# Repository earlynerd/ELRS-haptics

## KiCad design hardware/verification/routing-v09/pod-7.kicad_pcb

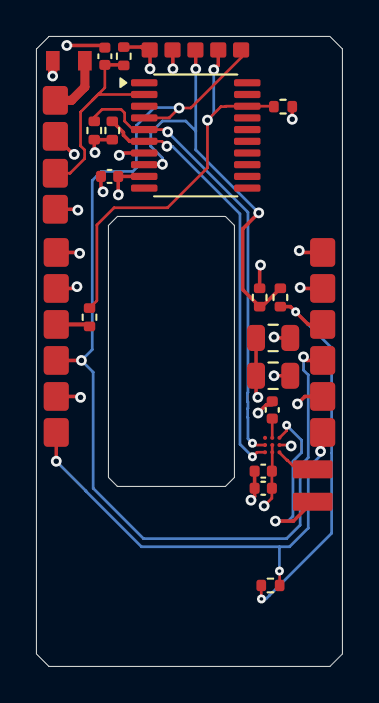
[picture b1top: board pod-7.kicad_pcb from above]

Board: 4 copper layers, 17.0 x 35.0 mm, 24 parts (0 on the bottom side), 16 nets.

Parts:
C26, C27, C170: 100n; C_0402_1005Metric
C28: 1u; C_0402_1005Metric
C171: 10u; C_0805_2012Metric
C172: 10n; C_0402_1005Metric
C173: 22u 10V X5R; C_0805_2012Metric
F107: 250mA FAST; Fuse_Littelfuse_467_0603
J128: CHAIN IN; WirePads_6_P2mm
J129: CHAIN OUT; WirePads_6_P2mm
J130: ICE / INITIAL FLASH; WirePads_5_P1.27mm
J131: NTC (optional); WirePads_2_P2mm
J207: PROTECTED CELL 90mAh; WirePads_2_P2mm
M8: VLV041235L; Vybronics_VLV041235L_FPC_Contact_Draft
R22, R23: 4.7k; R_0402_1005Metric
R53, R170: 0; R_0402_1005Metric
R171: 33; R_0402_1005Metric
R172, R173: 100k; R_0402_1005Metric
R175: 10k 1%; R_0402_1005Metric
U10: DRV2625; DRV2625_YFF_9_0.4mm
U25: M2003FC1AE; TSSOP-20_4.4x6.5mm_P0.65mm

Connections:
/Eight ring pods/Pod 7 / U25/CELL_POS: F107.1, J207.1
/Eight ring pods/Pod 7 / U25/CELL_TEMP: C172.1, J131.1, R175.2, U25.2
/Eight ring pods/Pod 7 / U25/DRV_REG: C27.1, U10.A2
/Eight ring pods/Pod 7 / U25/LOCAL_SCL: R23.2, U10.C1, U25.6
/Eight ring pods/Pod 7 / U25/LOCAL_SDA: R22.2, U10.B1, U25.5
/Eight ring pods/Pod 7 / U25/LRA_N: M8.2, U10.C3
/Eight ring pods/Pod 7 / U25/LRA_P: M8.1, U10.A3
/Eight ring pods/Pod 7 / U25/UART_RX_LOCAL: J130.4, R170.2, R172.2, U25.18
/Eight ring pods/Pod 7 / U25/UART_TX_LOCAL: J130.3, R171.1, R173.2, U25.8
GND: C26.2, C27.2, C28.2, C170.2, C171.2, C172.2, C173.2, J128.2, J129.2, J130.2, J131.2, J207.2, U10.B3, U25.7
POD_3V3: C26.1, C28.1, C170.1, C171.1, C173.1, J128.1, J129.1, J130.1, R22.1, R23.1, R172.1, R173.1, R175.1, U10.B2, U10.C2, U25.9
RING_D7: J128.3, R170.1
RING_D8: J129.3, R53.1, R171.2
RING_RETURN: J128.6, J129.6, R53.2
RING_nRESET: J128.4, J129.4, J130.5, U25.4
VBAT: F107.2, J128.5, J129.5
